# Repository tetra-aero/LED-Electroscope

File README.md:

# LED-Electroscope
This is pcb about LED Electroscope

### Operation
- LED ON when insert Hot (Live), AC100V
- LED OFF when insert Neural, AC100V and not inserting.

## Reference
1. http://bbradio.sakura.ne.jp/kanden/kanden.html

## Board
### Top

### Back

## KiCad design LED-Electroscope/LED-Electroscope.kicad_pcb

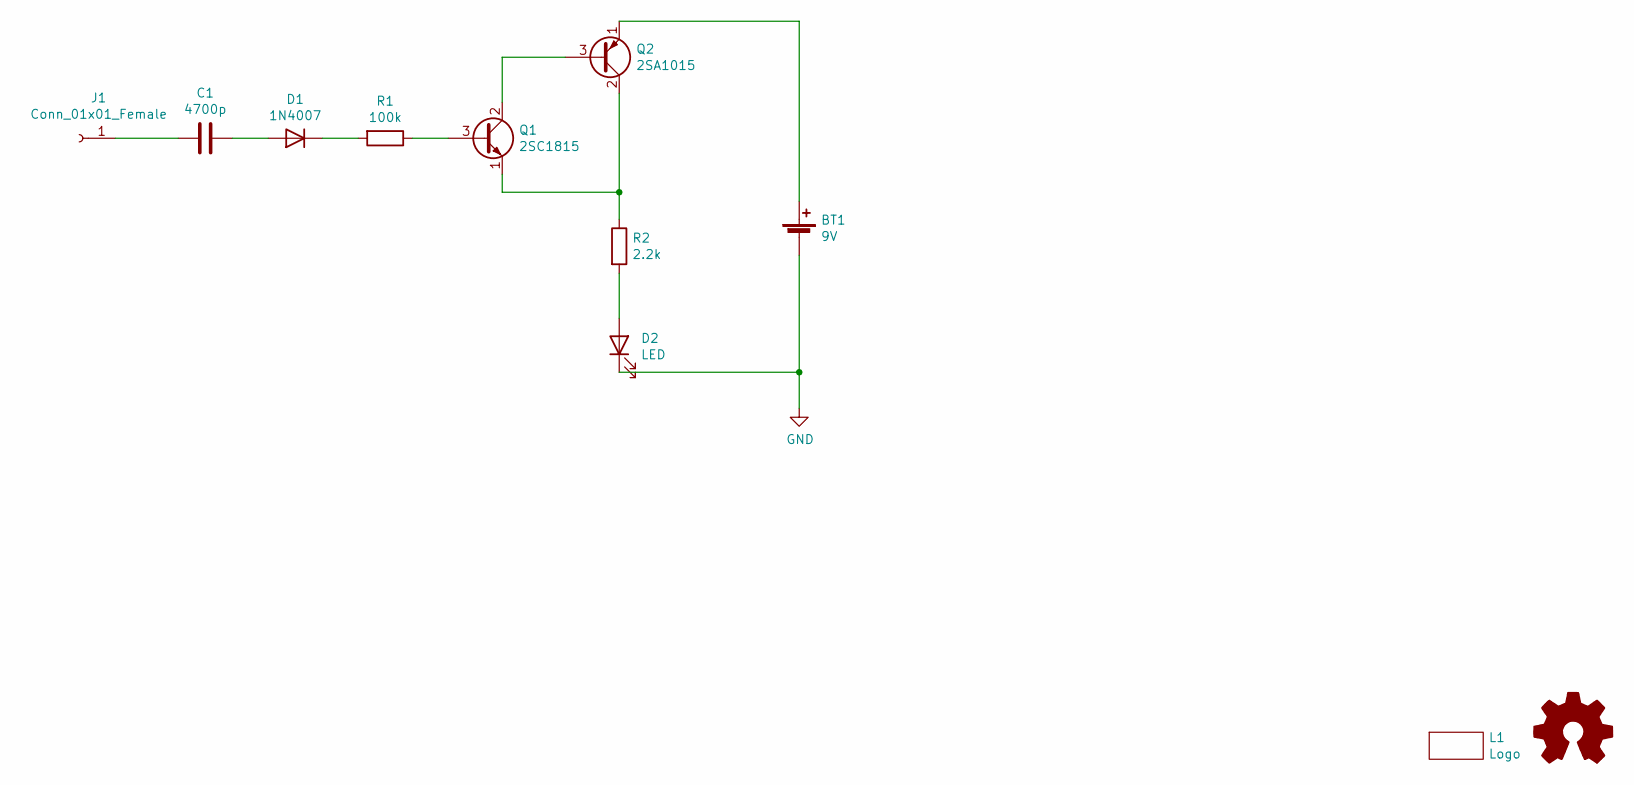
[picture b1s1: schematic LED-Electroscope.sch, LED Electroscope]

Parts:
BT1: 9V; PinHeader_1x02_P2.54mm_Vertical
C1: 4700p; C_Disc_D5.0mm_W2.5mm_P5.00mm
D1: 1N4007; D_A-405_P7.62mm_Horizontal
D2: LED; LED_D5.0mm
J1: Conn_01x01_Female; Terminal_100V_Hole_2.5mm_Pad
L1: Logo; teTra-logo
Q1: 2SC1815; TO-92_Inline
Q2: 2SA1015; TO-92_Inline
R1: 100k; R_Axial_DIN0207_L6.3mm_D2.5mm_P2.54mm_Vertical
R2: 2.2k; R_Axial_DIN0207_L6.3mm_D2.5mm_P2.54mm_Vertical

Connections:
GND: BT1.2 (-), D2.1 (K)
unnamed: BT1.1 (+), Q2.1 (E)
unnamed: C1.1, D1.2 (A)
unnamed: C1.2, J1.1
unnamed: D1.1 (K), R1.2
unnamed: D2.2 (A), R2.2
unnamed: Q1.1 (E), Q2.2 (C), R2.1
unnamed: Q1.2 (C), Q2.3 (B)
unnamed: Q1.3 (B), R1.1

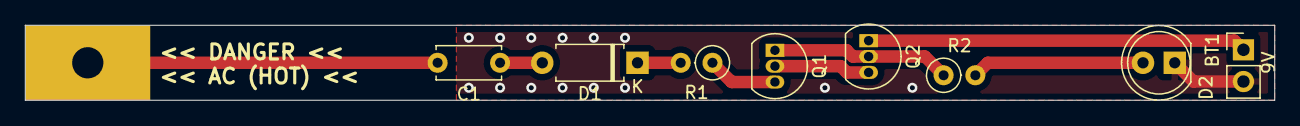
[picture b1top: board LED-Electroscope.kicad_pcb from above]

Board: 2 copper layers, 100.0 x 6.0 mm, 10 parts (1 on the bottom side), 9 nets.

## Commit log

2021-10-29 add v1.0.0
    add v1.0.0
2021-10-29 fix #1, add description
    fix #1, add description
2021-10-30 order 1.0.1
    order 1.0.1
2021-11-25 add photo, board v1
    add photo, board v1
2021-11-25 fix write method
    fix write method
2021-11-25 add photo in operation
    add photo in operation
2021-11-25 fix readme
    fix readme
2021-11-25 add description in readme
    add description in readme
